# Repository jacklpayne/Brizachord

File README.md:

Demo: https://www.youtube.com/watch?v=z-tGAeBtxNY

# Overview
The Brizachord is an open-source instrument and chord machine inspired by the Suzuki Omnichord. It features:
* 240 possible chords from 12 root select switches, 4 quality select switches, and 5 extension select switches
* Drum machine triggered by internal sequencer with toggleable chord pattern synchronization ("Groove"), adjustable BPM
* Velocity sensitive, multitouch capacitive strum plate for autoharp-style use
* Self-contained design with its own digital oscillators, amplification, and speaker (i.e, *not* a MIDI-only type deal).

It was designed by me and will be used in workshops held with the Audio Engineering Society at the University of Florida in Fall 2025.

# Technical
The instrument is based on the Daisy Seed audio development board and the associated `libdaisy` library for programming its STM32H7 MCU. It uses a Bela Trill Bar sensor for the strum plate and an Adafruit PAM8302A Class-D breakout for the amplifier. 

The hardware is designed for removability and reuse of the Daisy Seed and the Trill Bar.

# Future
## Software:
* Improve documentation of all functions
* USB MIDI (important)
* MIDI clock synchronization
* Data-driven CSV reading for sequencer patterns so that users can create their own more easily

## Hardware:
* Adjust Trill Bar JST cutout position
* Change corner mounting holes to M3 sized
* Find 12mm switches that are compatible with large black/white circular & square bezels to use for root selects, pattern selects
* Remove unused speaker routing holes and move Trill Bar headers to bottom of board
* Onboard power is possible, but unlikely to be implemented by me on this iteration of the board

# Environment setup
The firmware is based on a custom fork of `libdaisy` that updates the language version to `C++17` and merges @giulomoro's Trill support PR (https://github.com/electro-smith/libDaisy/pull/657). When this PR is merged upstream, the project will probably migrate to standard `libdaisy`.

# License
All software/firmware is licensed under GPLv3.
All hardware (schematic, design) is licensed under CERN-OHL-S.

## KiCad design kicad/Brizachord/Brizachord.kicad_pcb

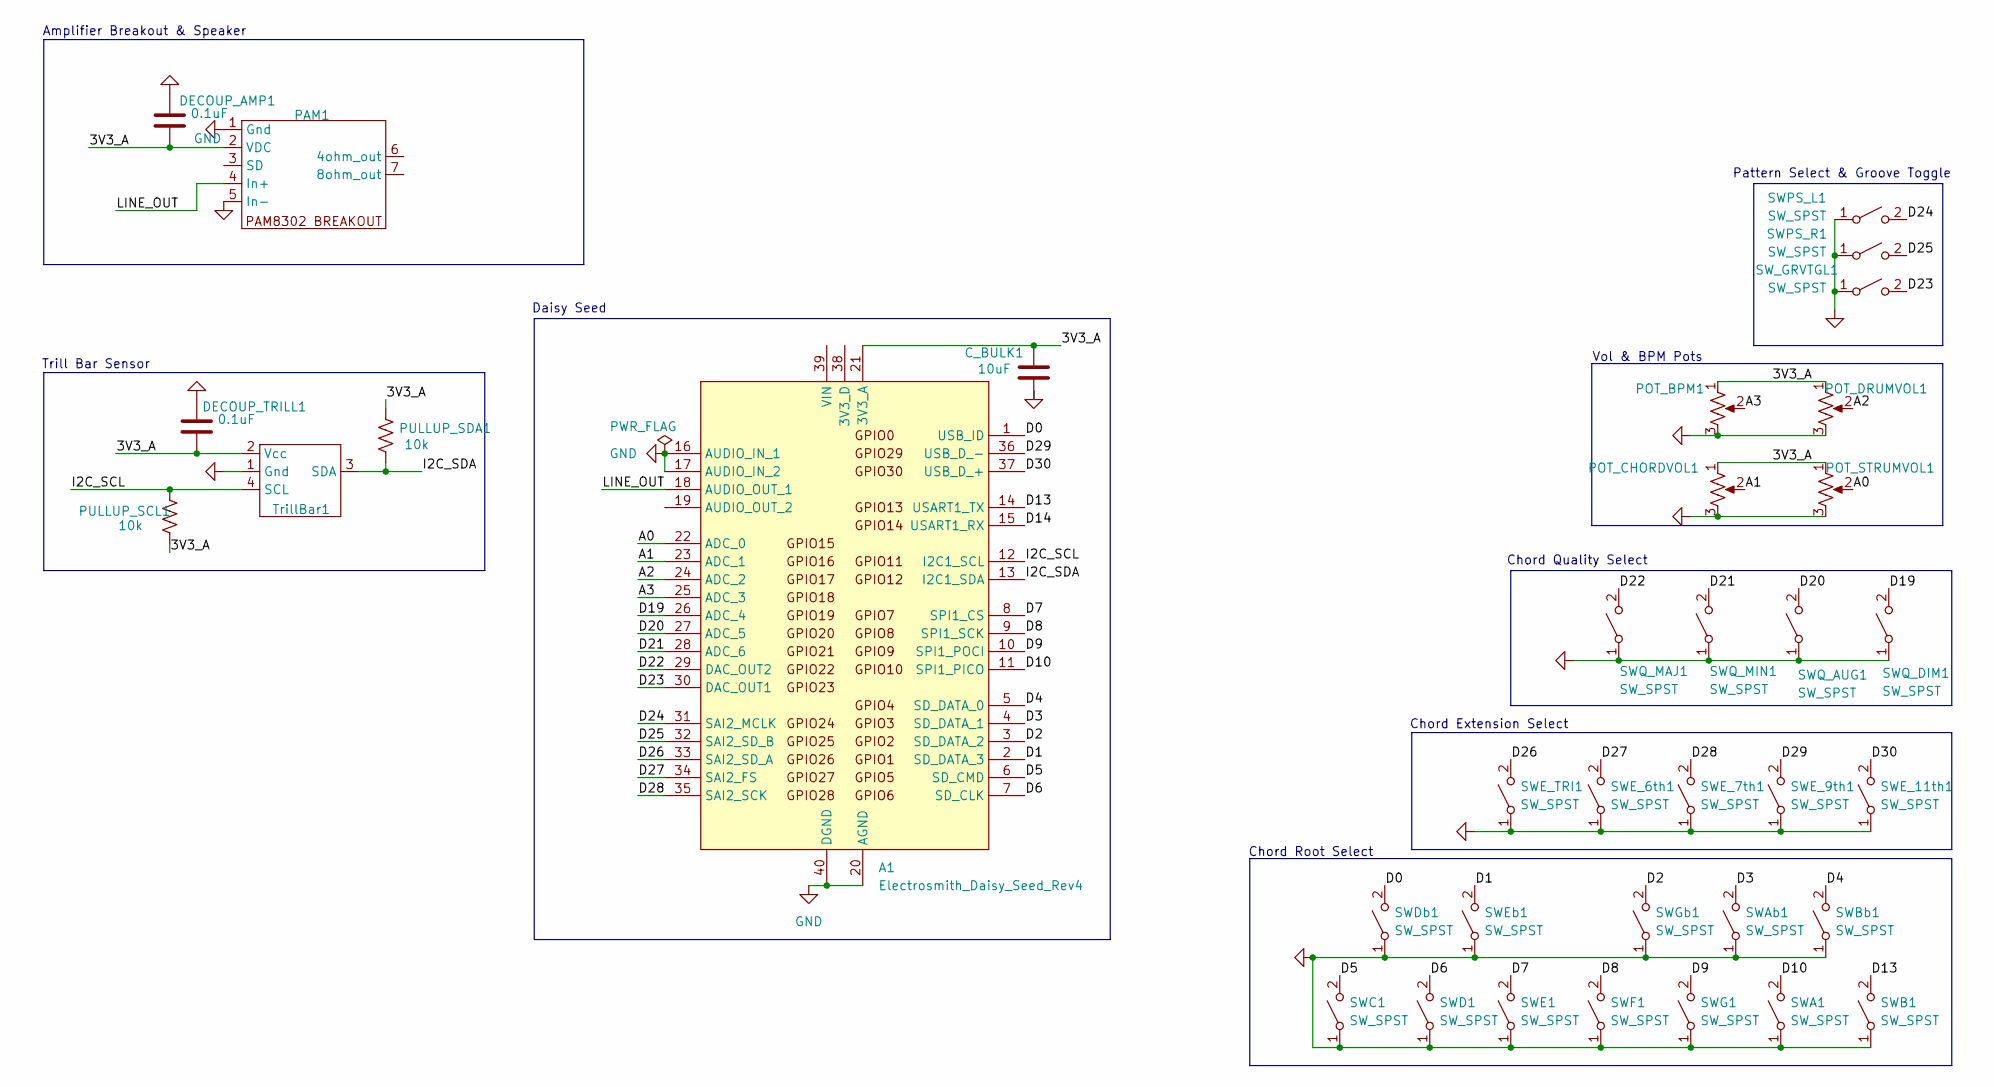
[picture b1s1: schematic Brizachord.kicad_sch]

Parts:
A1: Electrosmith_Daisy_Seed_Rev4; Electrosmith_Daisy_Seed
C_BULK1: 10uF; R_Axial_DIN0204_L3.6mm_D1.6mm_P7.62mm_Horizontal
DECOUP_AMP1: 0.1uF; R_Axial_DIN0204_L3.6mm_D1.6mm_P7.62mm_Horizontal
DECOUP_TRILL1: 0.1uF; R_Axial_DIN0204_L3.6mm_D1.6mm_P7.62mm_Horizontal
PAM1: PAM8302_BREAKOUT
POT_BPM1: R_Potentiometer_US; Samtec_HPM-03-01-x-S_Straight_1x03_Pitch5.08mm
POT_CHORDVOL1: R_Potentiometer_US; Samtec_HPM-03-01-x-S_Straight_1x03_Pitch5.08mm
POT_DRUMVOL1: R_Potentiometer_US; Samtec_HPM-03-01-x-S_Straight_1x03_Pitch5.08mm
POT_STRUMVOL1: R_Potentiometer_US; Samtec_HPM-03-01-x-S_Straight_1x03_Pitch5.08mm
PULLUP_SCL1: 10k; R_Axial_DIN0204_L3.6mm_D1.6mm_P5.08mm_Horizontal
PULLUP_SDA1: 10k; R_Axial_DIN0204_L3.6mm_D1.6mm_P5.08mm_Horizontal
SWA1: SW_SPST; SW_PUSH-12mm
SWAb1: SW_SPST; SW_PUSH-12mm
SWB1: SW_SPST; SW_PUSH-12mm
SWBb1: SW_SPST; SW_PUSH-12mm
SWC1: SW_SPST; SW_PUSH-12mm
SWD1: SW_SPST; SW_PUSH-12mm
SWDb1: SW_SPST; SW_PUSH-12mm
SWE1: SW_SPST; SW_PUSH-12mm
SWE_6th1, SWE_7th1, SWE_9th1, SWE_11th1: SW_SPST; SW_PUSH-12mm
SWE_TRI1: SW_SPST; SW_PUSH-12mm
SWEb1: SW_SPST; SW_PUSH-12mm
SWF1: SW_SPST; SW_PUSH-12mm
SWG1: SW_SPST; SW_PUSH-12mm
SWGb1: SW_SPST; SW_PUSH-12mm
SWPS_L1: SW_SPST; SW_PUSH-12mm
SWPS_R1: SW_SPST; SW_PUSH-12mm
SWQ_AUG1: SW_SPST; SW_PUSH-12mm
SWQ_DIM1: SW_SPST; SW_PUSH-12mm
SWQ_MAJ1: SW_SPST; SW_PUSH-12mm
SWQ_MIN1: SW_SPST; SW_PUSH-12mm
SW_GRVTGL1: SW_SPST; SW_PUSH-12mm
TrillBar1: PinHeader_1x04_P2.54mm_Vertical

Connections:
/3V3_A: A1.21 (3V3_A), C_BULK1.2, DECOUP_AMP1.1, DECOUP_TRILL1.1, PAM1.2 (VDC), POT_BPM1.1, POT_CHORDVOL1.1, POT_DRUMVOL1.1, POT_STRUMVOL1.1, PULLUP_SCL1.2, PULLUP_SDA1.1, TrillBar1.2 (Vcc)
/A0: A1.22 (ADC_0), POT_STRUMVOL1.2
/A1: A1.23 (ADC_1), POT_CHORDVOL1.2
/A2: A1.24 (ADC_2), POT_DRUMVOL1.2
/A3: A1.25 (ADC_3), POT_BPM1.2
/D0: A1.1 (USB_ID), SWDb1.2 (B)
/D1: A1.2 (SD_DATA_3), SWEb1.2 (B)
/D2: A1.3 (SD_DATA_2), SWGb1.2 (B)
/D3: A1.4 (SD_DATA_1), SWAb1.2 (B)
/D4: A1.5 (SD_DATA_0), SWBb1.2 (B)
/D5: A1.6 (SD_CMD), SWC1.2 (B)
/D6: A1.7 (SD_CLK), SWD1.2 (B)
/D7: A1.8 (SPI1_CS), SWE1.2 (B)
/D8: A1.9 (SPI1_SCK), SWF1.2 (B)
/D9: A1.10 (SPI1_POCI), SWG1.2 (B)
/D10: A1.11 (SPI1_PICO), SWA1.2 (B)
/D13: A1.14 (USART1_TX), SWB1.2 (B)
/D14: A1.15 (USART1_RX)
/D19: A1.26 (ADC_4), SWQ_DIM1.2 (B)
/D20: A1.27 (ADC_5), SWQ_AUG1.2 (B)
/D21: A1.28 (ADC_6), SWQ_MIN1.2 (B)
/D22: A1.29 (DAC_OUT2), SWQ_MAJ1.2 (B)
/D23: A1.30 (DAC_OUT1), SW_GRVTGL1.2 (B)
/D24: A1.31 (SAI2_MCLK), SWPS_L1.2 (B)
/D25: A1.32 (SAI2_SD_B), SWPS_R1.2 (B)
/D26: A1.33 (SAI2_SD_A), SWE_TRI1.2 (B)
/D27: A1.34 (SAI2_FS), SWE_6th1.2 (B)
/D28: A1.35 (SAI2_SCK), SWE_7th1.2 (B)
/D29: A1.36 (USB_D_-), SWE_9th1.2 (B)
/D30: A1.37 (USB_D_+), SWE_11th1.2 (B)
/I2C_SCL: A1.12 (I2C1_SCL), PULLUP_SCL1.1, TrillBar1.4 (SCL)
/I2C_SDA: A1.13 (I2C1_SDA), PULLUP_SDA1.2, TrillBar1.3 (SDA)
/LINE_OUT: A1.18 (AUDIO_OUT_1), PAM1.4 (In+)
GND: A1.16 (AUDIO_IN_1), A1.17 (AUDIO_IN_2), A1.20 (AGND), A1.40 (DGND), C_BULK1.1, DECOUP_AMP1.2, DECOUP_TRILL1.2, PAM1.1 (Gnd), PAM1.5 (In-), POT_BPM1.3, POT_CHORDVOL1.3, POT_DRUMVOL1.3, POT_STRUMVOL1.3, SWA1.1 (A), SWAb1.1 (A), SWB1.1 (A), SWBb1.1 (A), SWC1.1 (A), SWD1.1 (A), SWDb1.1 (A), SWE1.1 (A), SWE_6th1.1 (A), SWE_7th1.1 (A), SWE_9th1.1 (A), SWE_11th1.1 (A), SWE_TRI1.1 (A), SWEb1.1 (A), SWF1.1 (A), SWG1.1 (A), SWGb1.1 (A), SWPS_L1.1 (A), SWPS_R1.1 (A), SWQ_AUG1.1 (A), SWQ_DIM1.1 (A), SWQ_MAJ1.1 (A), SWQ_MIN1.1 (A), SW_GRVTGL1.1 (A), TrillBar1.1 (Gnd)

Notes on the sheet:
Chord Extension Select
Chord Quality Select
Vol & BPM Pots
Daisy Seed
Trill Bar Sensor
Chord Root Select
Pattern Select & Groove Toggle
Amplifier Breakout & Speaker

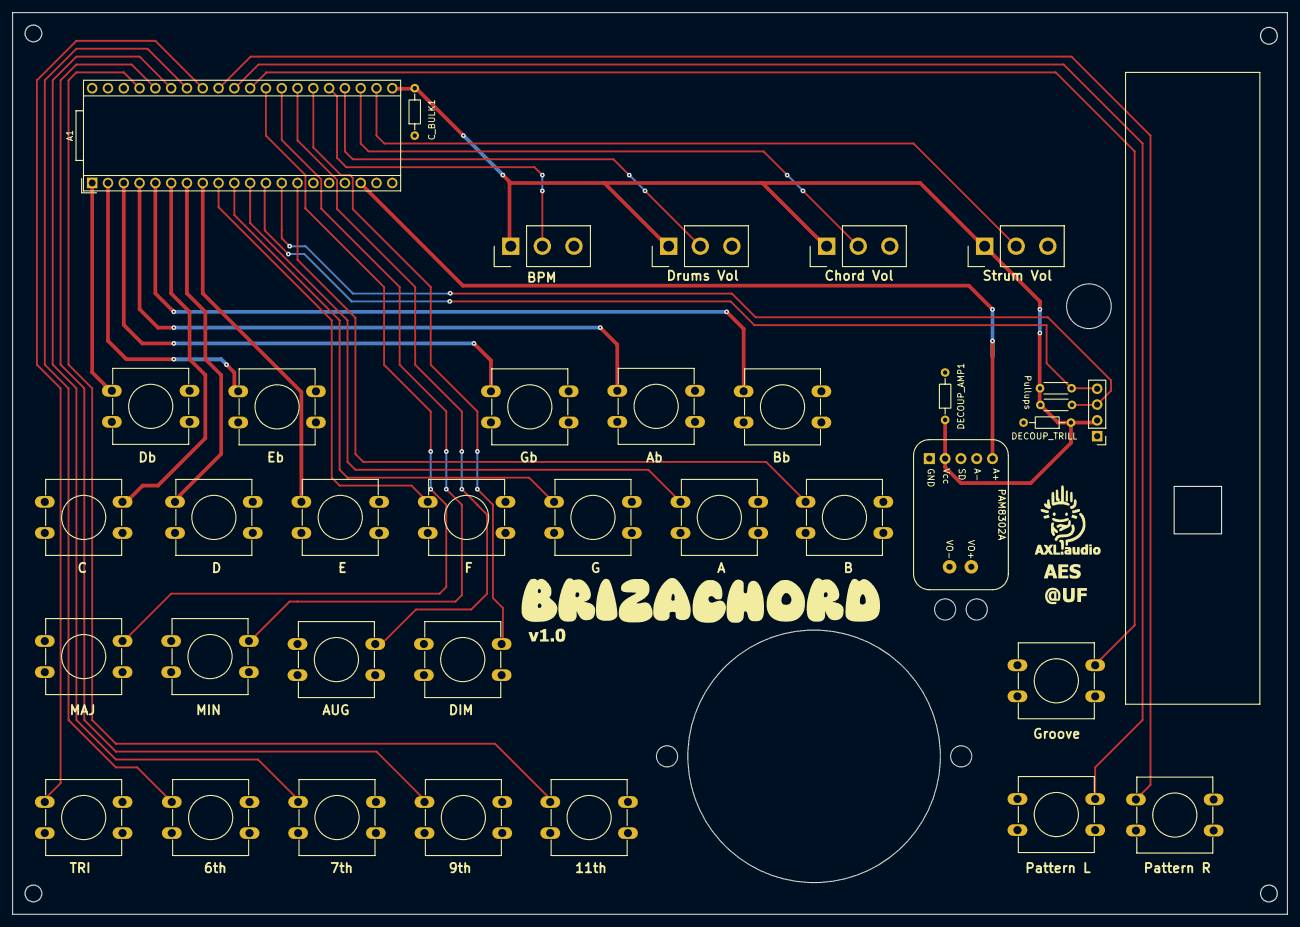
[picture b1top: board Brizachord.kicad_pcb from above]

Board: 2 copper layers, 205.0 x 145.0 mm, 36 parts (0 on the bottom side), 33 nets.

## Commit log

2025-07-25 Init
2025-07-26 Poll pots
    Implements polling potentiometer values and logarithmic scaling
2025-07-26 Pot poll
    Implement polling potentiometer values and applying volume scaling and bpm adjustment. Volume range adjustment and bpm update in sequencer still needed
2025-07-27 Adjust pot range
    Adjusts potentiometer range. Also updates sequencer BPM in main loop.
2025-07-27 Sequences & groove toggle
    Refactors and implements sequences, sequence scrolling, and groove toggling
2025-07-27 Adjust sounds
    Tweaks to all sound sources
2025-07-28 Add more sequences
    Implements a few sequences/patterns
2025-07-28 Remove erroneous files
    Oopsy daisy.
2025-07-29 Small sound tweaks
    Tweaks some filters
2025-07-29 Fix extension buttons
2025-07-31 Fix crash on startup
    Addresses crash on startup issue by replacing pointers with class members
2025-08-03 Bass sequencing
    Implement scale-from-chord generation, bass voice triggering, and bass voice sequencing
2025-08-03 Add bass sequences
    Adds bass sequences for each existing pattern
2025-08-06 Readme update
    Add demo to readme
2025-08-06 Fix readme
    Update readme
2025-08-07 Add hardware files
    Adds the Kicad project files to the repo
2025-08-07 Repo refactor
    Add /build and other extraneous files to gitignore & move source to /src
2025-08-07 Update .gitignore
    Omits editor files from repo
2025-08-07 Clean repo cache
2025-08-07 Remove scripts
    Remove old/erroneous scripts
2025-08-07 Add image to readme
2025-08-30 Adjust chord range
    Reduce A, Bb, B by an octave to keep chords in similar range
2025-08-30 Adjust strum synth behavior
    Change strum synth oscillators to not update their frequencies until retriggered by a strum on a chord change
